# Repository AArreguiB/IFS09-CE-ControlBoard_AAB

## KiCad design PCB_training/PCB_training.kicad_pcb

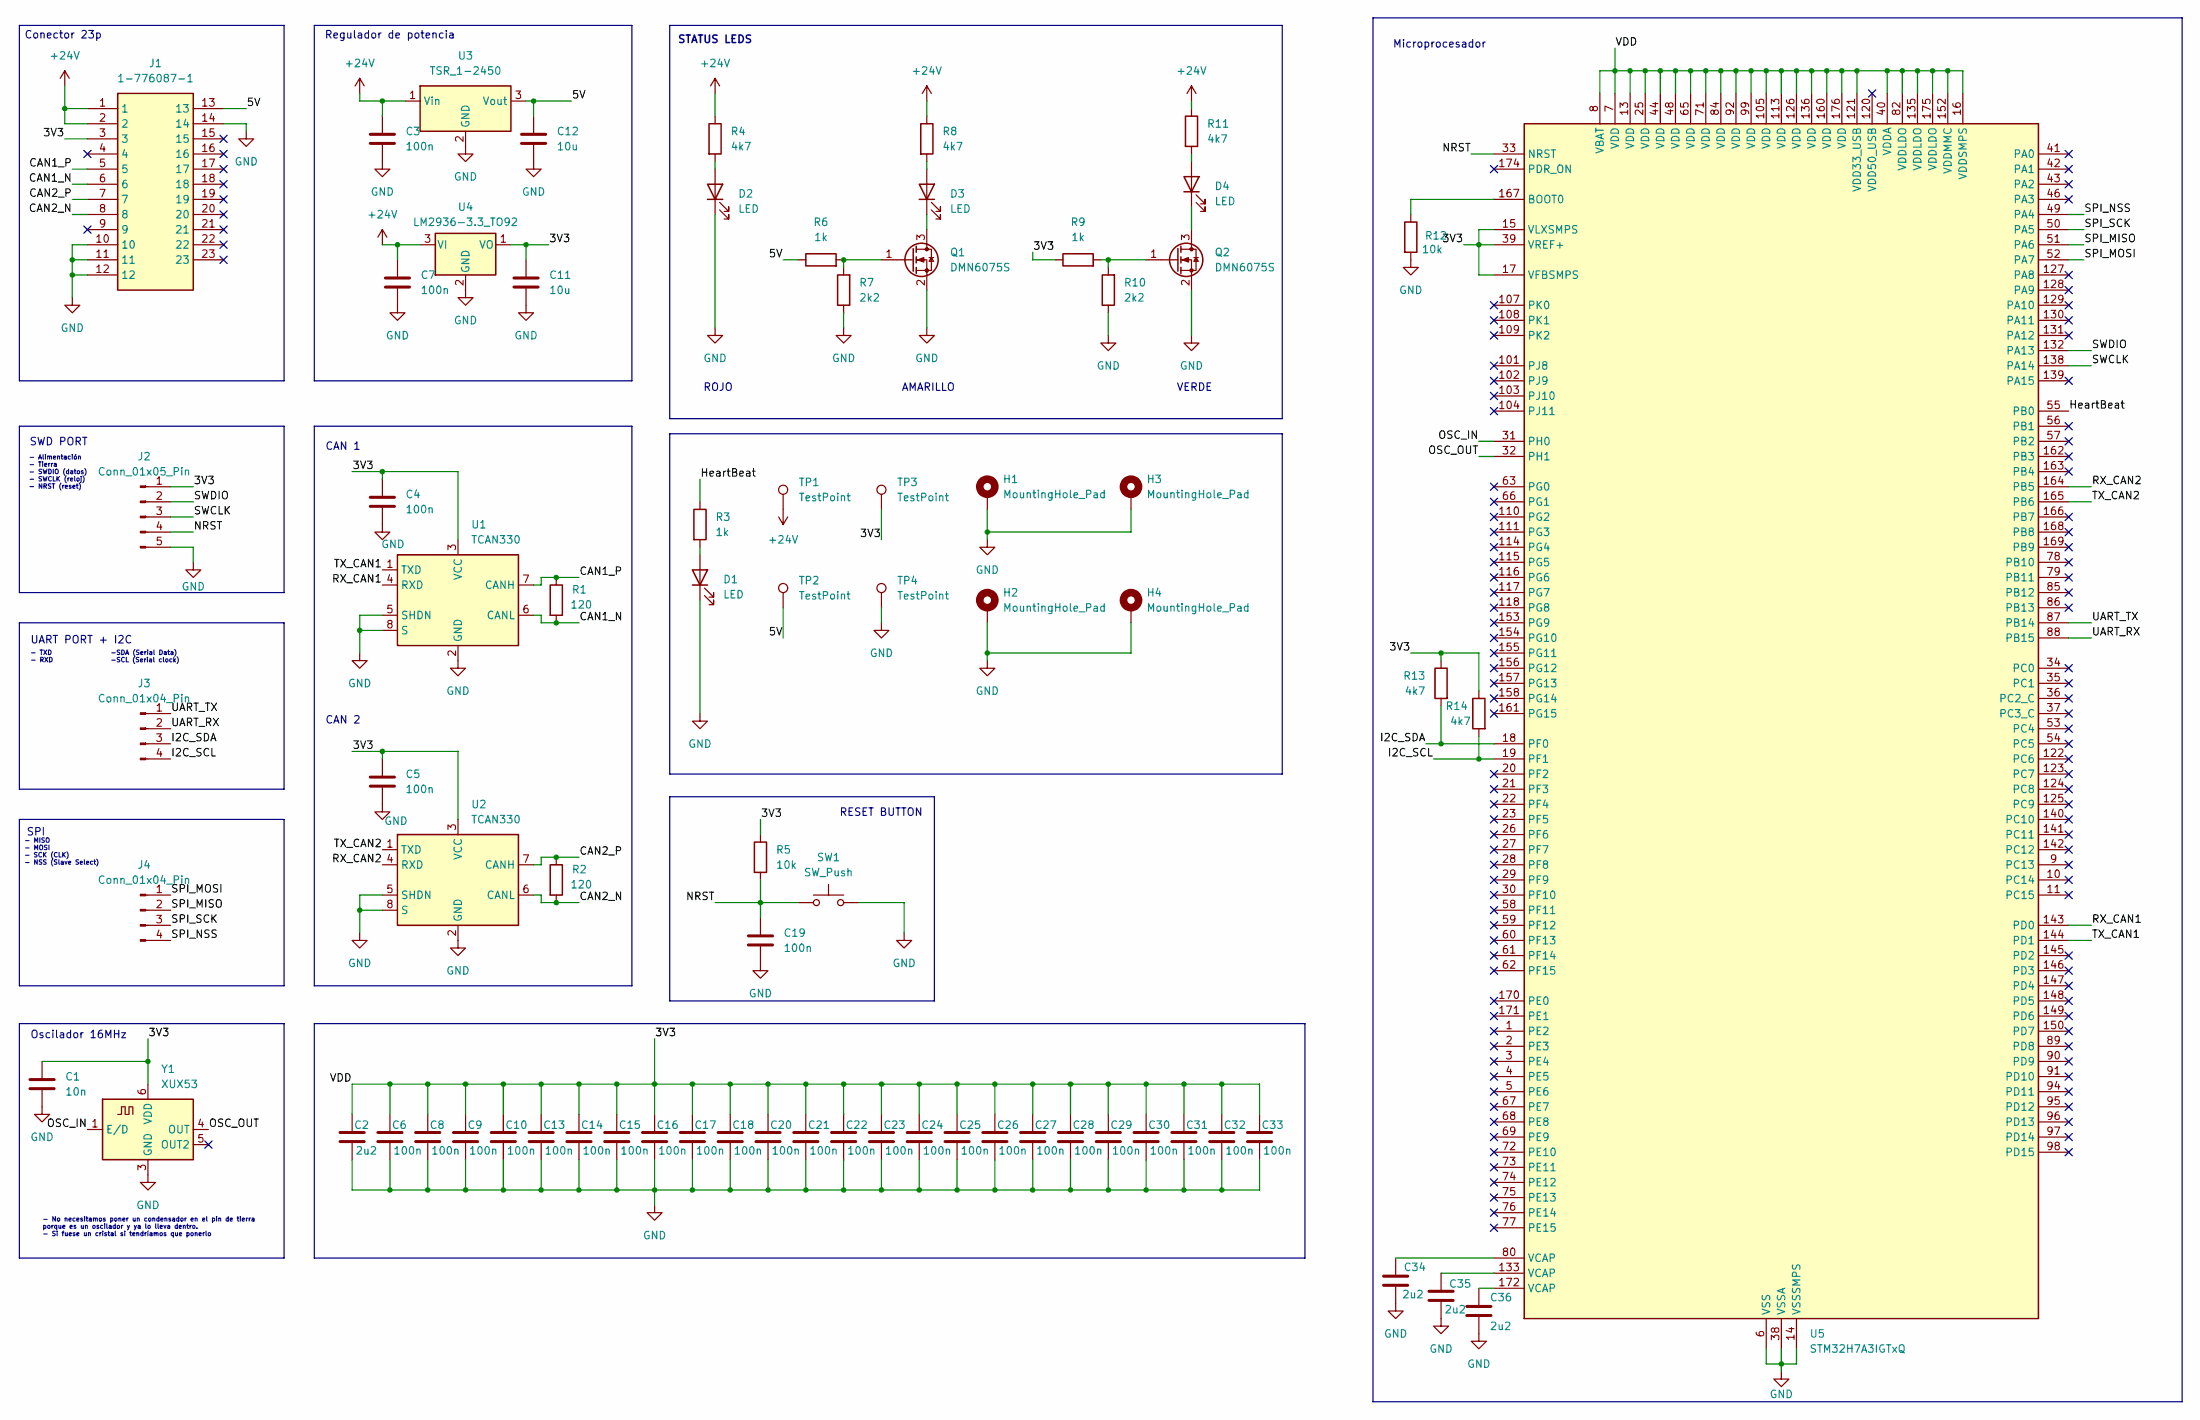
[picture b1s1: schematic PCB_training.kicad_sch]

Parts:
C1: 10n; C_0805_2012Metric_Pad1.18x1.45mm_HandSolder
C2, C34, C35, C36: 2u2; C_0805_2012Metric_Pad1.18x1.45mm_HandSolder
C3, C4, C5, C6, C7, C8, C9, C10, C13, C14, C15, C16, C17, C18, C19, C20, C21, C22, C23, C24, C25, C26, C27, C28, C29, C30, C31, C32, C33: 100n; C_0805_2012Metric_Pad1.18x1.45mm_HandSolder
C11, C12: 10u; C_0805_2012Metric_Pad1.18x1.45mm_HandSolder
D1, D2, D3, D4: LED; LED_1206_3216Metric_Pad1.42x1.75mm_HandSolder
H1, H2, H3, H4: MountingHole_Pad; MountingHole_3.2mm_M3_Pad
J1: 1-776087-1; 17760871; Mouser Part Number 571-1-776087-1
J2: Conn_01x05_Pin; PinHeader_1x05_P2.54mm_Vertical
J3, J4: Conn_01x04_Pin; PinHeader_1x04_P2.54mm_Vertical
Q1, Q2: DMN6075S; SOT-23
R1, R2: 120; R_0805_2012Metric_Pad1.20x1.40mm_HandSolder
R3, R6, R9: 1k; R_0805_2012Metric_Pad1.20x1.40mm_HandSolder
R4, R8, R11, R13, R14: 4k7; R_0805_2012Metric_Pad1.20x1.40mm_HandSolder
R5, R12: 10k; R_0805_2012Metric_Pad1.20x1.40mm_HandSolder
R7, R10: 2k2; R_0805_2012Metric_Pad1.20x1.40mm_HandSolder
SW1: SW_Push; Panasonic_EVQPUK_EVQPUB
TP1, TP2, TP3, TP4: TestPoint; TestPoint_Pad_D2.0mm
U1, U2: TCAN330; SOIC-8_3.9x4.9mm_P1.27mm
U3: TSR_1-2450; Converter_DCDC_TRACO_TSR-1_THT
U4: LM2936-3.3_TO92; TO-92_Inline
U5: STM32H7A3IGTxQ; LQFP-176_24x24mm_P0.5mm
Y1: XUX53; Oscillator_SMD_IDT_JS6-6_5.0x3.2mm_P1.27mm

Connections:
+24V: C3.1, C7.1, J1.1, J1.2, R4.1, R8.1, R11.1, TP1.1 (1_1), U3.1 (Vin), U4.3 (VI)
/3V3: C1.1, C2.1, C4.1, C5.1, C6.1, C8.1, C9.1, C10.1, C11.1, C13.1, C14.1, C15.1, C16.1, C17.1, C18.1, C20.1, C21.1, C22.1, C23.1, C24.1, C25.1, C26.1, C27.1, C28.1, C29.1, C30.1, C31.1, C32.1, C33.1, J1.3, J2.1, R5.1, R9.1, R13.1, R14.1, TP3.1 (1_1), U1.3 (VCC), U2.3 (VCC), U4.1 (VO), U5.7 (VDD), U5.8 (VBAT), U5.13 (VDD), U5.15 (VLXSMPS), U5.16 (VDDSMPS), U5.17 (VFBSMPS), U5.25 (VDD), U5.39 (VREF+), U5.40 (VDDA), U5.44 (VDD), U5.48 (VDD), U5.65 (VDD), U5.71 (VDD), U5.82 (VDDLDO), U5.84 (VDD), U5.92 (VDD), U5.99 (VDD), U5.105 (VDD), U5.113 (VDD), U5.121 (VDD33_USB), U5.126 (VDD), U5.135 (VDDLDO), U5.136 (VDD), U5.152 (VDDMMC), U5.160 (VDD), U5.175 (VDDLDO), U5.176 (VDD), Y1.6 (VDD)
/5V: C12.1, J1.13, R6.1, TP2.1 (1_1), U3.3 (Vout)
/CAN1_N: J1.6, R1.2, U1.6 (CANL)
/CAN1_P: J1.5, R1.1, U1.7 (CANH)
/CAN2_N: J1.8, R2.2, U2.6 (CANL)
/CAN2_P: J1.7, R2.1, U2.7 (CANH)
/HeartBeat: R3.1, U5.55 (PB0)
/I2C_SCL: J3.4, R14.2, U5.19 (PF1)
/I2C_SDA: J3.3, R13.2, U5.18 (PF0)
/NRST: C19.1, J2.4, R5.2, SW1.1, U5.33 (NRST)
/OSC_IN: U5.31 (PH0), Y1.1 (E/D)
/OSC_OUT: U5.32 (PH1), Y1.4 (OUT)
/RX_CAN1: U1.4 (RXD), U5.143 (PD0)
/RX_CAN2: U2.4 (RXD), U5.164 (PB5)
/SPI_MISO: J4.2, U5.51 (PA6)
/SPI_MOSI: J4.1, U5.52 (PA7)
/SPI_NSS: J4.4, U5.49 (PA4)
/SPI_SCK: J4.3, U5.50 (PA5)
/SWCLK: J2.3, U5.138 (PA14)
/SWDIO: J2.2, U5.132 (PA13)
/TX_CAN1: U1.1 (TXD), U5.144 (PD1)
/TX_CAN2: U2.1 (TXD), U5.165 (PB6)
/UART_RX: J3.2, U5.88 (PB15)
/UART_TX: J3.1, U5.87 (PB14)
GND: C1.2, C2.2, C3.2, C4.2, C5.2, C6.2, C7.2, C8.2, C9.2, C10.2, C11.2, C12.2, C13.2, C14.2, C15.2, C16.2, C17.2, C18.2, C19.2, C20.2, C21.2, C22.2, C23.2, C24.2, C25.2, C26.2, C27.2, C28.2, C29.2, C30.2, C31.2, C32.2, C33.2, C34.2, C35.2, C36.2, D1.1 (K), D2.1 (K), H1.1 (1_1), H2.1 (1_1), H3.1 (1_1), H4.1 (1_1), J1.10, J1.11, J1.12, J1.14, J2.5, Q1.2 (S), Q2.2 (S), R7.1, R10.1, R12.2, SW1.2, TP4.1 (1_1), U1.2 (GND), U1.5 (SHDN), U1.8 (S), U2.2 (GND), U2.5 (SHDN), U2.8 (S), U3.2 (GND), U4.2 (GND), U5.6 (VSS), U5.12 (VSS), U5.14 (VSSSMPS), U5.24 (VSS), U5.38 (VSSA), U5.45 (VSS), U5.47 (VSS), U5.64 (VSS), U5.70 (VSS), U5.81 (VSS), U5.83 (VSS), U5.93 (VSS), U5.100 (VSS), U5.106 (VSS), U5.112 (VSS), U5.119 (VSS), U5.134 (VSS), U5.137 (VSS), U5.151 (VSS), U5.159 (VSS), U5.173 (VSS), Y1.3 (GND)
unnamed: C34.1, U5.80 (VCAP)
unnamed: C35.1, U5.133 (VCAP)
unnamed: C36.1, U5.172 (VCAP)
unnamed: D1.2 (A), R3.2
unnamed: D2.2 (A), R4.2
unnamed: D3.2 (A), R8.2
unnamed: D3.1 (K), Q1.3 (D)
unnamed: D4.2 (A), R11.2
unnamed: D4.1 (K), Q2.3 (D)
unnamed: Q1.1 (G), R6.2, R7.2
unnamed: Q2.1 (G), R9.2, R10.2
unnamed: R12.1, U5.167 (BOOT0)

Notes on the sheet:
Conector 23p
SWD PORT
- TXD - RXD
- Alimentación - Tierra - SWDIO (datos) - SWCLK (reloj) - NRST (reset)
Microprocesador
- MISO - MOSI - SCK (CLK) - NSS (Slave Select)
SPI
ROJO
RESET BUTTON
AMARILLO
-SDA (Serial Data) -SCL (Serial clock)
Oscilador 16MHz
VERDE
Regulador de potencia
CAN 1
UART PORT + I2C
- No necesitamos poner un condensador en el pin de tierra porque es un oscilador y ya lo lleva dentro. - Si fuese un cristal si tendríamos que ponerlo
STATUS LEDS
CAN 2

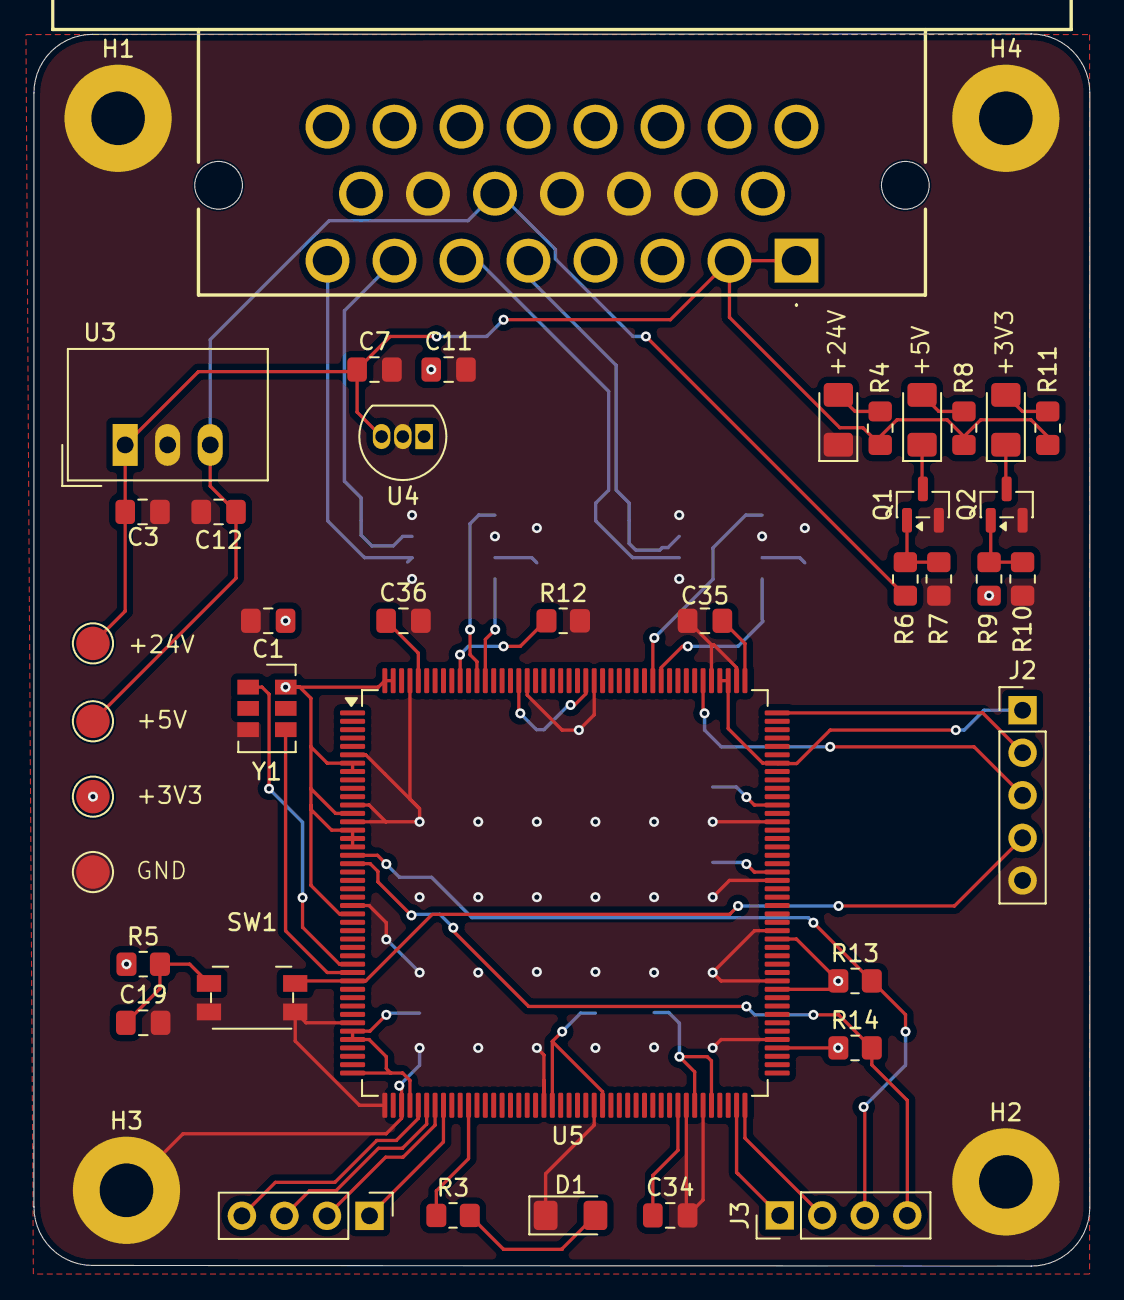
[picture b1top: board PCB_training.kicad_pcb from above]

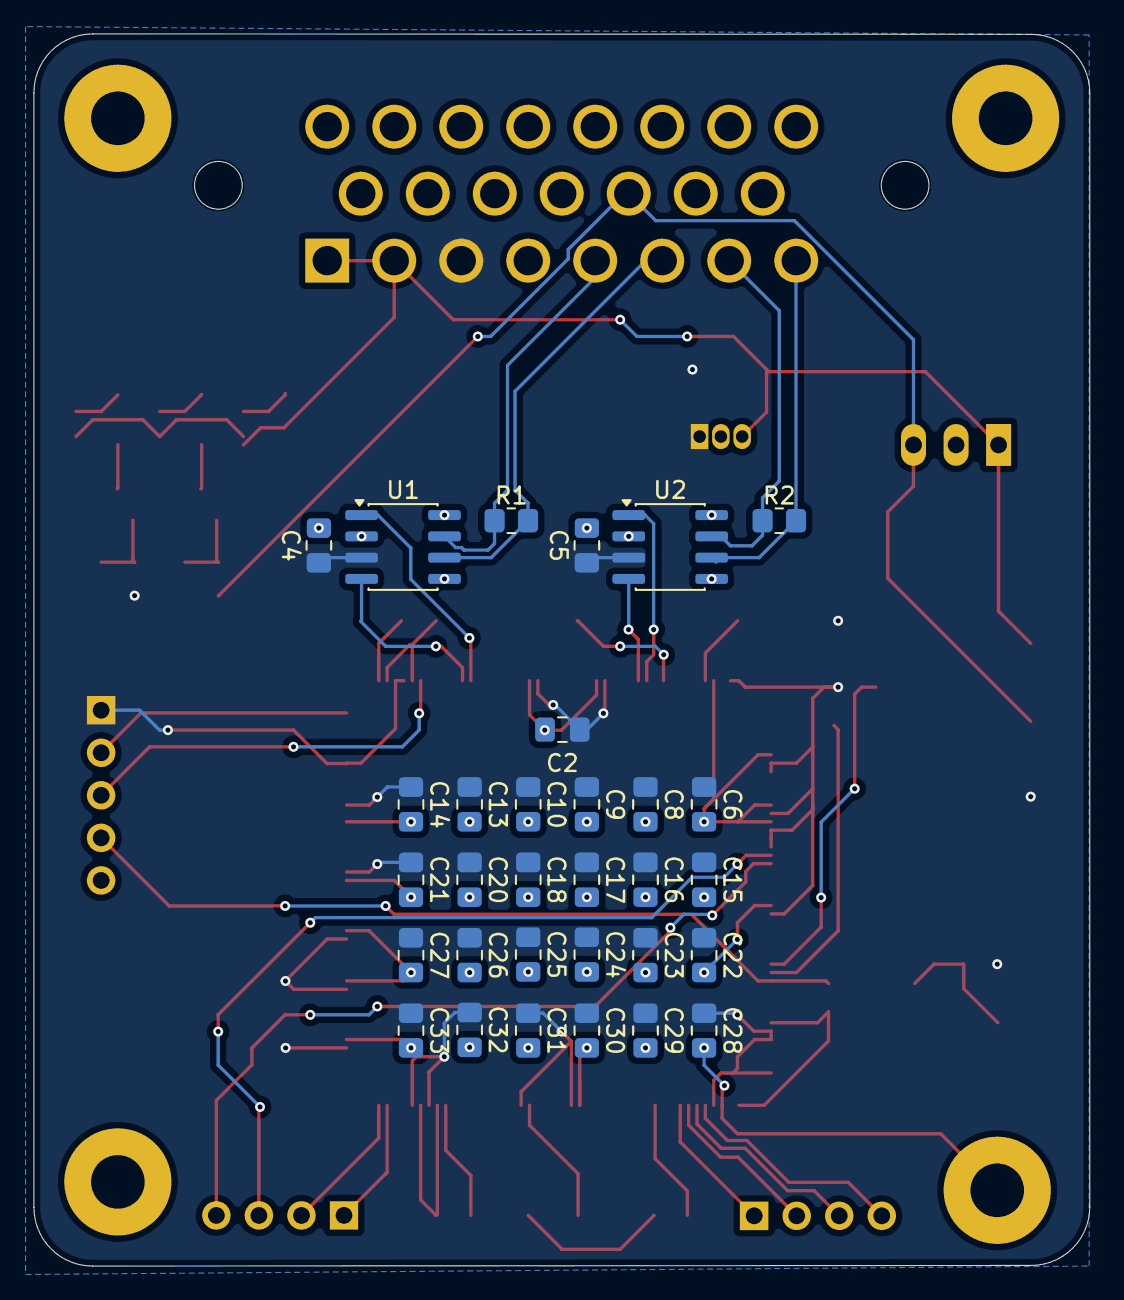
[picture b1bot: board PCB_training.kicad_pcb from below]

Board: 2 copper layers, 63.0 x 73.6 mm, 75 parts (31 on the bottom side), 38 nets.
